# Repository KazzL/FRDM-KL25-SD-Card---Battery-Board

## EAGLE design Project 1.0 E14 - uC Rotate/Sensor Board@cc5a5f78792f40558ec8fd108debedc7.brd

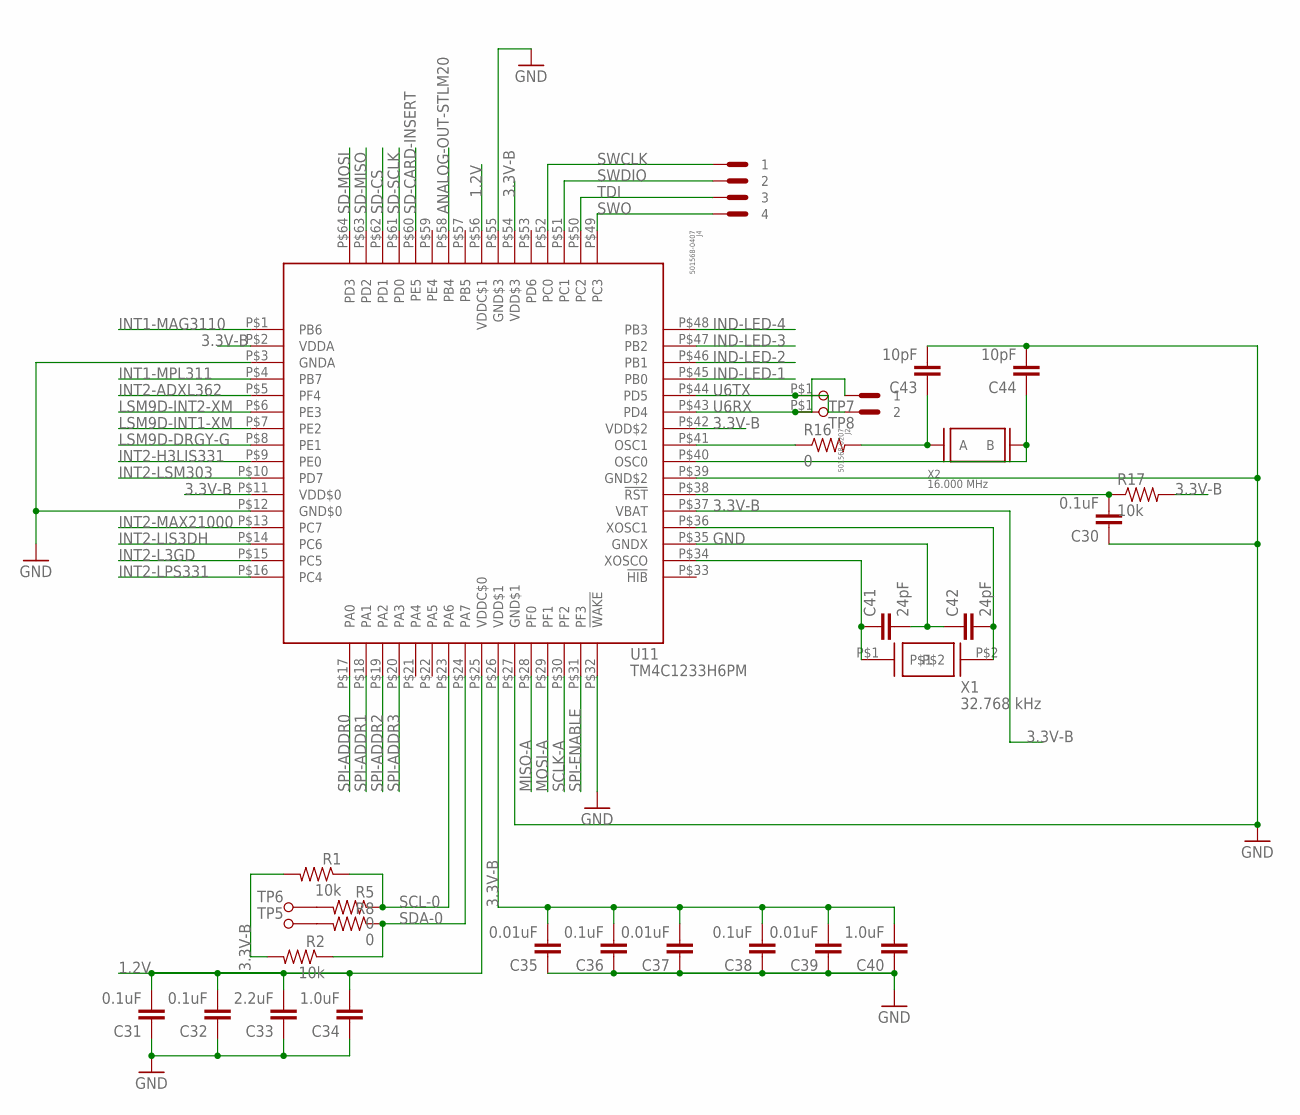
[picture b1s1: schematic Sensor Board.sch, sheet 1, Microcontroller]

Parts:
C30, C31, C32, C36, C38: 0.1uF; C0402
C33: 2.2uF; C0402
C34, C40: 1.0uF; C0402
C35, C37, C39: 0.01uF; C0402
C41, C42: 24pF; C0402
C43, C44: 10pF; C0402
J2: 501568-0207
J4: 501568-0407
R1, R2, R17: 10k; R0402
R5, R8, R16: 0; R0402
TP5, TP6, TP7, TP8: TESTPAD(ROUND)
U11: TM4C1233H6PM; S-PQFP-G64
X1: 32.768 kHz; 2-SMD(3.2X1.5)
X2: 16.000 MHz; 4-SMD(3.2X2.5)

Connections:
1.2V: C31.2, C32.2, C33.2, C34.2, U11.P$25 (VDDC$0), U11.P$56 (VDDC$1)
3.3V-B: C35.2, C36.2, C37.2, C38.2, C39.2, C40.2, R1.2, R2.2, R17.2, U11.P$2 (VDDA), U11.P$11 (VDD$0), U11.P$26 (VDD$1), U11.P$37 (VBAT), U11.P$42 (VDD$2), U11.P$54 (VDD$3); also elsewhere on the board
ANALOG-OUT-STLM20: U11.P$58 (PB4); also elsewhere on the board
GND: C30.1, C31.1, C32.1, C33.1, C34.1, C35.1, C36.1, C37.1, C38.1, C39.1, C40.1, C41.2, C42.1, C43.2, C44.2, U11.P$3 (GNDA), U11.P$12 (GND$0), U11.P$27 (GND$1), U11.P$32 (!WAKE), U11.P$35 (GNDX), U11.P$39 (GND$2), U11.P$55 (GND$3); also elsewhere on the board
IND-LED-1: U11.P$45 (PB0); also elsewhere on the board
IND-LED-2: U11.P$46 (PB1); also elsewhere on the board
IND-LED-3: U11.P$47 (PB2); also elsewhere on the board
IND-LED-4: U11.P$48 (PB3); also elsewhere on the board
INT1-MAG3110: U11.P$1 (PB6); also elsewhere on the board
INT1-MPL311: U11.P$4 (PB7); also elsewhere on the board
INT2-ADXL362: U11.P$5 (PF4); also elsewhere on the board
INT2-H3LIS331: U11.P$9 (PE0); also elsewhere on the board
INT2-L3GD: U11.P$15 (PC5); also elsewhere on the board
INT2-LIS3DH: U11.P$14 (PC6); also elsewhere on the board
INT2-LPS331: U11.P$16 (PC4); also elsewhere on the board
INT2-LSM303: U11.P$10 (PD7); also elsewhere on the board
INT2-MAX21000: U11.P$13 (PC7); also elsewhere on the board
LSM9D-DRGY-G: U11.P$8 (PE1); also elsewhere on the board
LSM9D-INT1-XM: U11.P$7 (PE2); also elsewhere on the board
LSM9D-INT2-XM: U11.P$6 (PE3); also elsewhere on the board
MISO-A: U11.P$28 (PF0); also elsewhere on the board
MOSI-A: U11.P$29 (PF1); also elsewhere on the board
unnamed: C30.2, R17.1, U11.P$38 (!RST)
unnamed: C42.2, U11.P$36 (XOSC1), X1.P$2
unnamed: C41.1, U11.P$34 (XOSCO), X1.P$1
unnamed: C43.1, R16.2, X2.P$1 (A)
unnamed: C44.1, U11.P$40 (OSC0), X2.P$3 (B)
unnamed: R16.1, U11.P$41 (OSC1)
unnamed: R5.2, TP6.P$1
unnamed: R8.2, TP5.P$1
SCL-0: R1.1, R5.1, U11.P$23 (PA6); also elsewhere on the board
SCLK-A: U11.P$30 (PF2); also elsewhere on the board
SD-CARD-INSERT: U11.P$60 (PE5); also elsewhere on the board
SD-CS: U11.P$62 (PD1); also elsewhere on the board
SD-MISO: U11.P$63 (PD2); also elsewhere on the board
SD-MOSI: U11.P$64 (PD3); also elsewhere on the board
SD-SCLK: U11.P$61 (PD0); also elsewhere on the board
SDA-0: R2.1, R8.1, U11.P$24 (PA7); also elsewhere on the board
SPI-ADDR0: U11.P$17 (PA0); also elsewhere on the board
SPI-ADDR1: U11.P$18 (PA1); also elsewhere on the board
SPI-ADDR2: U11.P$19 (PA2); also elsewhere on the board
SPI-ADDR3: U11.P$20 (PA3); also elsewhere on the board
SPI-ENABLE: U11.P$31 (PF3); also elsewhere on the board
SWCLK: J4.P$1 (1), U11.P$52 (PC0)
SWDIO: J4.P$2 (2), U11.P$51 (PC1)
SWO: J4.P$4 (4), U11.P$49 (PC3)
TDI: J4.P$3 (3), U11.P$50 (PC2)
U6RX: J2.P$1 (1), TP8.P$1, U11.P$43 (PD4)
U6TX: J2.P$2 (2), TP7.P$1, U11.P$44 (PD5)

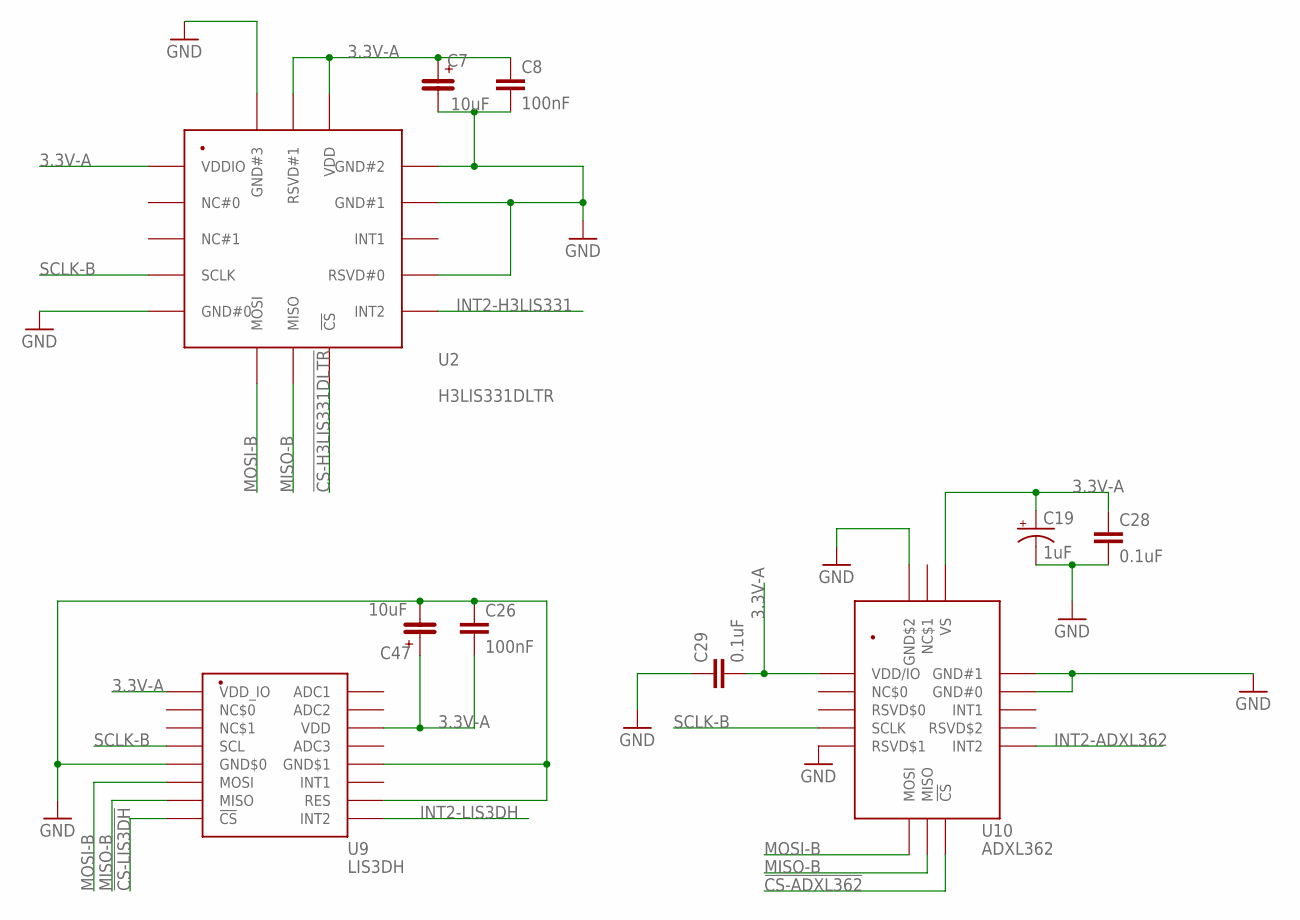
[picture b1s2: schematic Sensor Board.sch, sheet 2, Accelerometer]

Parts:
C7, C47: 10uF; 4.3X7.3SMD
C8, C26: 100nF; C0402
C19: 1uF; EIA6032
C28, C29: 0.1uF; C0402
U2: H3LIS331DLTR; LGA-16(3X3)
U9: LIS3DH; LGA-16(3X3)
U10: ADXL362; LGA-16(3X3.25)

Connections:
3.3V-A: C7.P$1, C8.1, C19.P$1 (+), C26.2, C28.1, C29.2, C47.P$1, U2.P$1 (VDDIO), U2.P$14 (VDD), U2.P$15 (RSVD#1), U9.P$1 (VDD_IO), U9.P$14 (VDD), U10.P$1 (VDD/IO), U10.P$14 (VS); also elsewhere on the board
!CS-ADXL362: U10.P$8 (!CS); also elsewhere on the board
!CS-H3LIS331DLTR: U2.P$8 (!CS); also elsewhere on the board
!CS-LIS3DH: U9.P$8 (!CS); also elsewhere on the board
GND: C7.P$2, C8.2, C19.P$2 (-), C26.1, C28.2, C29.1, C47.P$2, U2.P$5 (GND#0), U2.P$10 (RSVD#0), U2.P$12 (GND#1), U2.P$13 (GND#2), U2.P$16 (GND#3), U9.P$5 (GND$0), U9.P$10 (RES), U9.P$12 (GND$1), U10.P$5 (RSVD$1), U10.P$12 (GND#0), U10.P$13 (GND#1), U10.P$16 (GND$2); also elsewhere on the board
INT2-ADXL362: U10.P$9 (INT2); also elsewhere on the board
INT2-H3LIS331: U2.P$9 (INT2); also elsewhere on the board
INT2-LIS3DH: U9.P$9 (INT2); also elsewhere on the board
MISO-B: U2.P$7 (MISO), U9.P$7 (MISO), U10.P$7 (MISO); also elsewhere on the board
MOSI-B: U2.P$6 (MOSI), U9.P$6 (MOSI), U10.P$6 (MOSI); also elsewhere on the board
SCLK-B: U2.P$4 (SCLK), U9.P$4 (SCL), U10.P$4 (SCLK); also elsewhere on the board

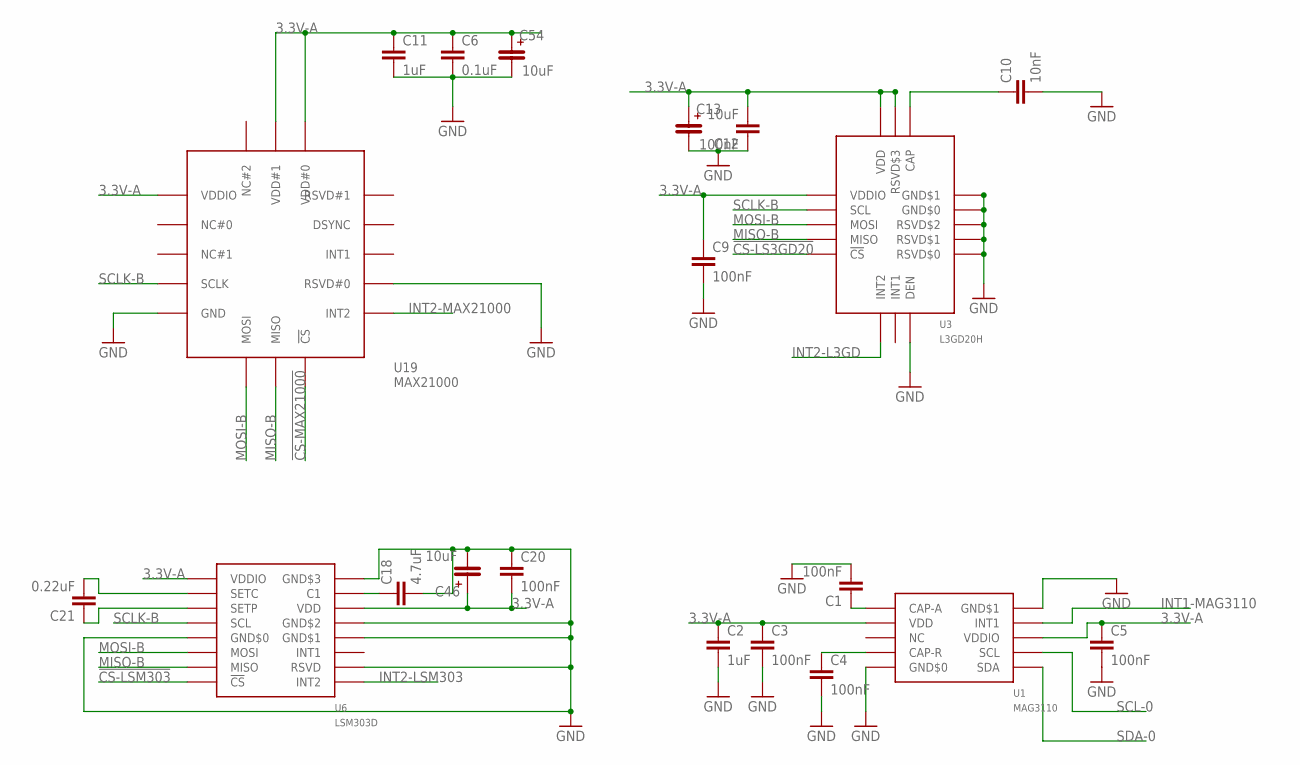
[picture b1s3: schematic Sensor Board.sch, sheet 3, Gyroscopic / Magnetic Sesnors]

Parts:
C1, C3, C4, C5, C9, C20: 100nF; C0402
C2, C11: 1uF; C0402
C6: 0.1uF; C0402
C10: 10nF; C0402
C12: 10uF; C0402
C13: 100nF; 4.3X7.3SMD
C18: 4.7uF; C0402
C21: 0.22uF; C0402
C46, C54: 10uF; 4.3X7.3SMD
U1: MAG3110; DFN-10(2X2)
U3: L3GD20H; LGA-16(3X3)
U6: LSM303D; LGA-16(3X3)
U19: MAX21000; LGA-16(3X3)

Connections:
3.3V-A: C2.1, C3.1, C5.1, C6.1, C9.1, C11.1, C12.2, C13.P$1, C20.2, C46.P$1, C54.P$1, U1.P$2 (VDD), U1.P$8 (VDDIO), U3.P$1 (VDDIO), U3.P$15 (RSVD$3), U3.P$16 (VDD), U6.P$1 (VDDIO), U6.P$14 (VDD), U19.P$1 (VDDIO), U19.P$14 (VDD#0), U19.P$15 (VDD#1); also elsewhere on the board
!CS-LS3GD20: U3.P$5 (!CS); also elsewhere on the board
!CS-LSM303: U6.P$8 (!CS); also elsewhere on the board
!CS-MAX21000: U19.P$8 (!CS); also elsewhere on the board
GND: C1.2, C2.2, C3.2, C4.2, C5.2, C6.2, C9.2, C10.2, C11.2, C12.1, C13.P$2, C18.2, C20.1, C46.P$2, C54.P$2, U1.P$5 (GND$0), U1.P$10 (GND$1), U3.P$8 (DEN), U3.P$9 (RSVD$0), U3.P$10 (RSVD$1), U3.P$11 (RSVD$2), U3.P$12 (GND$0), U3.P$13 (GND$1), U6.P$5 (GND$0), U6.P$10 (RSVD), U6.P$12 (GND$1), U6.P$13 (GND$2), U6.P$16 (GND$3), U19.P$5 (GND), U19.P$10 (RSVD#0); also elsewhere on the board
INT1-MAG3110: U1.P$9 (INT1); also elsewhere on the board
INT2-L3GD: U3.P$6 (INT2); also elsewhere on the board
INT2-LSM303: U6.P$9 (INT2); also elsewhere on the board
INT2-MAX21000: U19.P$9 (INT2); also elsewhere on the board
MISO-B: U3.P$4 (MISO), U6.P$7 (MISO), U19.P$7 (MISO); also elsewhere on the board
MOSI-B: U3.P$3 (MOSI), U6.P$6 (MOSI), U19.P$6 (MOSI); also elsewhere on the board
unnamed: C1.1, U1.P$1 (CAP-A)
unnamed: C4.1, U1.P$4 (CAP-R)
unnamed: C10.1, U3.P$14 (CAP)
unnamed: C18.1, U6.P$15 (C1)
unnamed: C21.2, U6.P$2 (SETC)
unnamed: C21.1, U6.P$3 (SETP)
SCL-0: U1.P$7 (SCL); also elsewhere on the board
SCLK-B: U3.P$2 (SCL), U6.P$4 (SCL), U19.P$4 (SCLK); also elsewhere on the board
SDA-0: U1.P$6 (SDA); also elsewhere on the board

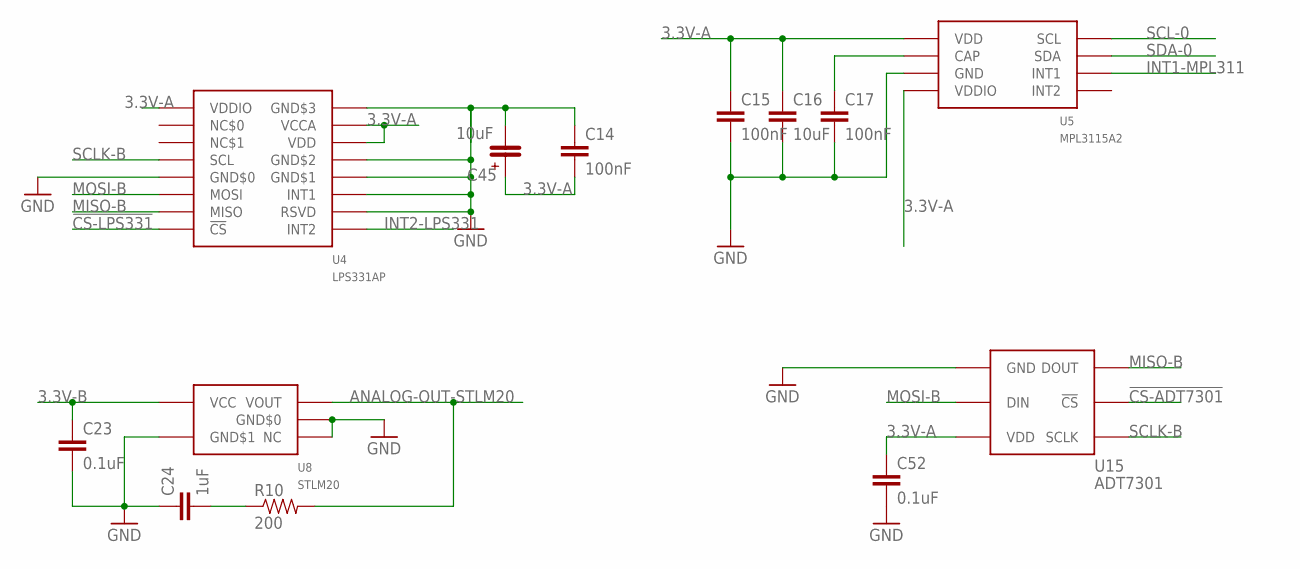
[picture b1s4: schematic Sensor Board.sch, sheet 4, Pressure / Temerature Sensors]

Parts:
C14, C15, C17: 100nF; C0402
C16: 10uF; C0402
C23, C52: 0.1uF; C0402
C24: 1uF; C0402
C45: 10uF; 4.3X7.3SMD
R10: 200; R0402
U4: LPS331AP; LGA-16(3X3)
U5: MPL3115A2; LGA-8(5X3)
U8: STLM20; SOT323-5L
U15: ADT7301; SOT23-6

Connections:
3.3V-A: C14.2, C15.1, C16.1, C45.P$1, C52.1, U4.P$1 (VDDIO), U4.P$14 (VDD), U4.P$15 (VCCA), U5.P$1 (VDD), U5.P$4 (VDDIO), U15.P$3 (VDD); also elsewhere on the board
3.3V-B: C23.1, U8.P$4 (VCC); also elsewhere on the board
!CS-ADT7301: U15.P$5 (!CS); also elsewhere on the board
!CS-LPS331: U4.P$8 (!CS); also elsewhere on the board
ANALOG-OUT-STLM20: R10.2, U8.P$3 (VOUT); also elsewhere on the board
GND: C14.1, C15.2, C16.2, C17.2, C23.2, C24.1, C45.P$2, C52.2, U4.P$5 (GND$0), U4.P$10 (RSVD), U4.P$11 (INT1), U4.P$12 (GND$1), U4.P$13 (GND$2), U4.P$16 (GND$3), U5.P$3 (GND), U8.P$1 (NC), U8.P$2 (GND$0), U8.P$5 (GND$1), U15.P$1 (GND); also elsewhere on the board
INT1-MPL311: U5.P$6 (INT1); also elsewhere on the board
INT2-LPS331: U4.P$9 (INT2); also elsewhere on the board
MISO-B: U4.P$7 (MISO), U15.P$6 (DOUT); also elsewhere on the board
MOSI-B: U4.P$6 (MOSI), U15.P$2 (DIN); also elsewhere on the board
unnamed: C17.1, U5.P$2 (CAP)
unnamed: C24.2, R10.1
SCL-0: U5.P$8 (SCL); also elsewhere on the board
SCLK-B: U4.P$4 (SCL), U15.P$4 (SCLK); also elsewhere on the board
SDA-0: U5.P$7 (SDA); also elsewhere on the board

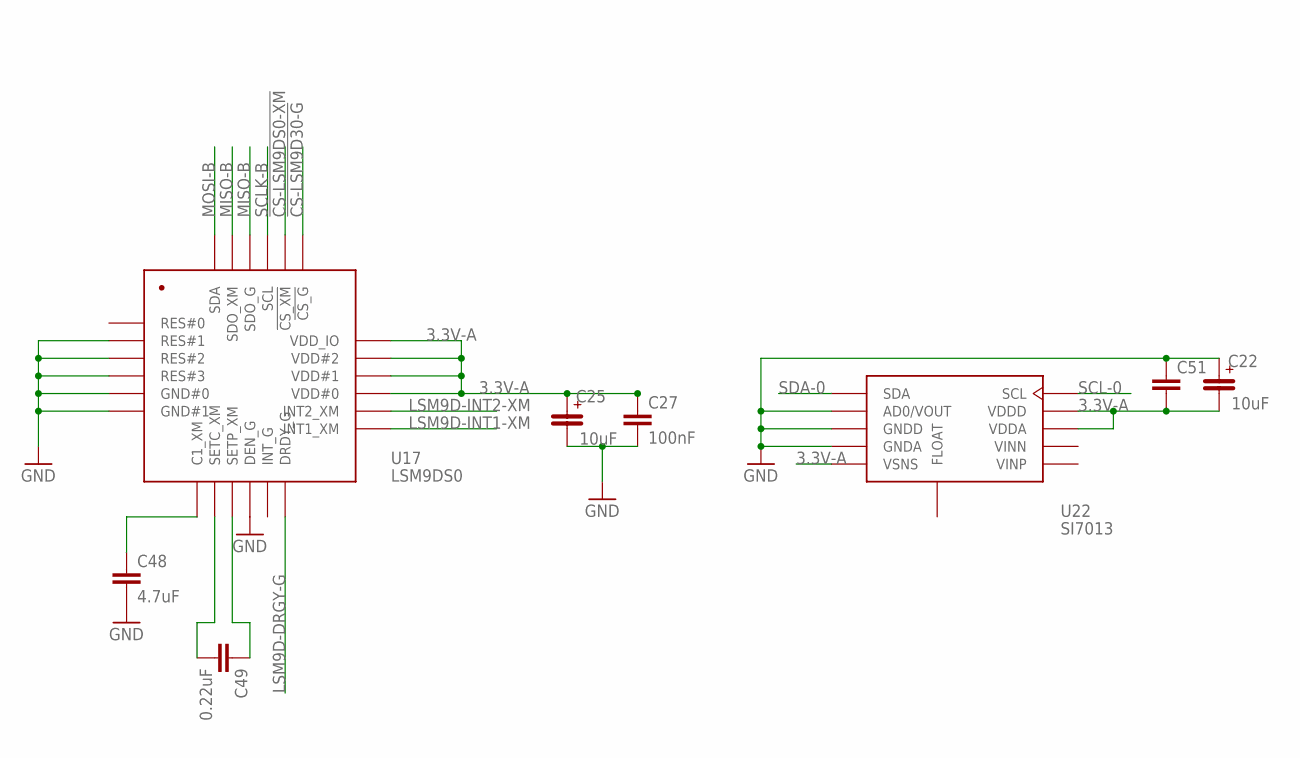
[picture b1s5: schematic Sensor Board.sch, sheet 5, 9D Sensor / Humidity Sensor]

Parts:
C22, C25: 10uF; 4.3X7.3SMD
C27: 100nF; C0402
C48: 4.7uF; C0402
C49: 0.22uF; C0402
C51: CAPACITOR0402; C0402
U17: LSM9DS0; LGA-24(4X4)
U22: SI7013; DFN-10(3X3)

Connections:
3.3V-A: C22.P$2, C25.P$1, C27.1, C51.2, U17.P$15 (VDD#0), U17.P$16 (VDD#1), U17.P$17 (VDD#2), U17.P$18 (VDD_IO), U22.P$5 (VSNS), U22.P$8 (VDDA), U22.P$9 (VDDD); also elsewhere on the board
!CS-LSM9D30-G: U17.P$19 (!CS_G); also elsewhere on the board
!CS-LSM9DS0-XM: U17.P$20 (!CS_XM); also elsewhere on the board
GND: C22.P$1, C25.P$2, C27.2, C48.2, C51.1, U17.P$2 (RES#1), U17.P$3 (RES#2), U17.P$4 (RES#3), U17.P$5 (GND#0), U17.P$6 (GND#1), U17.P$10 (DEN_G), U22.P$2 (AD0/VOUT), U22.P$3 (GNDD), U22.P$4 (GNDA); also elsewhere on the board
LSM9D-DRGY-G: U17.P$12 (DRDY_G); also elsewhere on the board
LSM9D-INT1-XM: U17.P$13 (INT1_XM); also elsewhere on the board
LSM9D-INT2-XM: U17.P$14 (INT2_XM); also elsewhere on the board
MISO-B: U17.P$22 (SDO_G), U17.P$23 (SDO_XM); also elsewhere on the board
MOSI-B: U17.P$24 (SDA); also elsewhere on the board
unnamed: C48.1, U17.P$7 (C1_XM)
unnamed: C49.2, U17.P$8 (SETC_XM)
unnamed: C49.1, U17.P$9 (SETP_XM)
SCL-0: U22.P$10 (SCL); also elsewhere on the board
SCLK-B: U17.P$21 (SCL); also elsewhere on the board
SDA-0: U22.P$1 (SDA); also elsewhere on the board

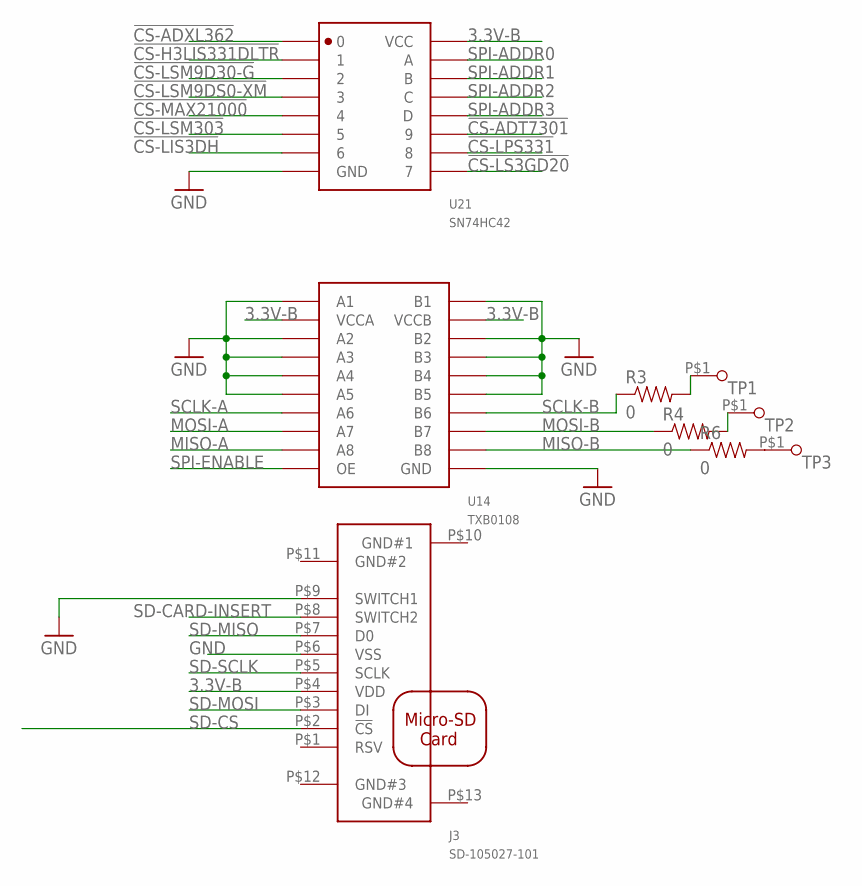
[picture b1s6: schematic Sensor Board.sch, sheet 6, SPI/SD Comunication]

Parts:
J3: SD-105027-101; SD-105027-1001
R3, R4, R6: 0; R0402
TP1, TP2, TP3: TESTPAD(ROUND)
U14: TXB0108; TSSOP-(PW)-20
U21: SN74HC42; SOIC-16

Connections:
3.3V-B: J3.P$4 (VDD), U14.P$2 (VCCA), U14.P$19 (VCCB), U21.P$16 (VCC); also elsewhere on the board
!CS-ADT7301: U21.P$11 (9); also elsewhere on the board
!CS-ADXL362: U21.P$1 (0); also elsewhere on the board
!CS-H3LIS331DLTR: U21.P$2 (1); also elsewhere on the board
!CS-LIS3DH: U21.P$7 (6); also elsewhere on the board
!CS-LPS331: U21.P$10 (8); also elsewhere on the board
!CS-LS3GD20: U21.P$9 (7); also elsewhere on the board
!CS-LSM9D30-G: U21.P$3 (2); also elsewhere on the board
!CS-LSM9DS0-XM: U21.P$4 (3); also elsewhere on the board
!CS-LSM303: U21.P$6 (5); also elsewhere on the board
!CS-MAX21000: U21.P$5 (4); also elsewhere on the board
GND: J3.P$6 (VSS), J3.P$9 (SWITCH1), U14.P$1 (A1), U14.P$3 (A2), U14.P$4 (A3), U14.P$5 (A4), U14.P$6 (A5), U14.P$11 (GND), U14.P$15 (B5), U14.P$16 (B4), U14.P$17 (B3), U14.P$18 (B2), U14.P$20 (B1), U21.P$8 (GND); also elsewhere on the board
MISO-A: U14.P$9 (A8); also elsewhere on the board
MISO-B: R6.1, U14.P$12 (B8); also elsewhere on the board
MOSI-A: U14.P$8 (A7); also elsewhere on the board
MOSI-B: R4.1, U14.P$13 (B7); also elsewhere on the board
unnamed: R3.2, TP1.P$1
unnamed: R4.2, TP2.P$1
unnamed: R6.2, TP3.P$1
SCLK-A: U14.P$7 (A6); also elsewhere on the board
SCLK-B: R3.1, U14.P$14 (B6); also elsewhere on the board
SD-CARD-INSERT: J3.P$8 (SWITCH2); also elsewhere on the board
SD-CS: J3.P$2 (!CS); also elsewhere on the board
SD-MISO: J3.P$7 (D0); also elsewhere on the board
SD-MOSI: J3.P$3 (DI); also elsewhere on the board
SD-SCLK: J3.P$5 (SCLK); also elsewhere on the board
SPI-ADDR0: U21.P$15 (A); also elsewhere on the board
SPI-ADDR1: U21.P$14 (B); also elsewhere on the board
SPI-ADDR2: U21.P$13 (C); also elsewhere on the board
SPI-ADDR3: U21.P$12 (D); also elsewhere on the board
SPI-ENABLE: U14.P$10 (OE); also elsewhere on the board

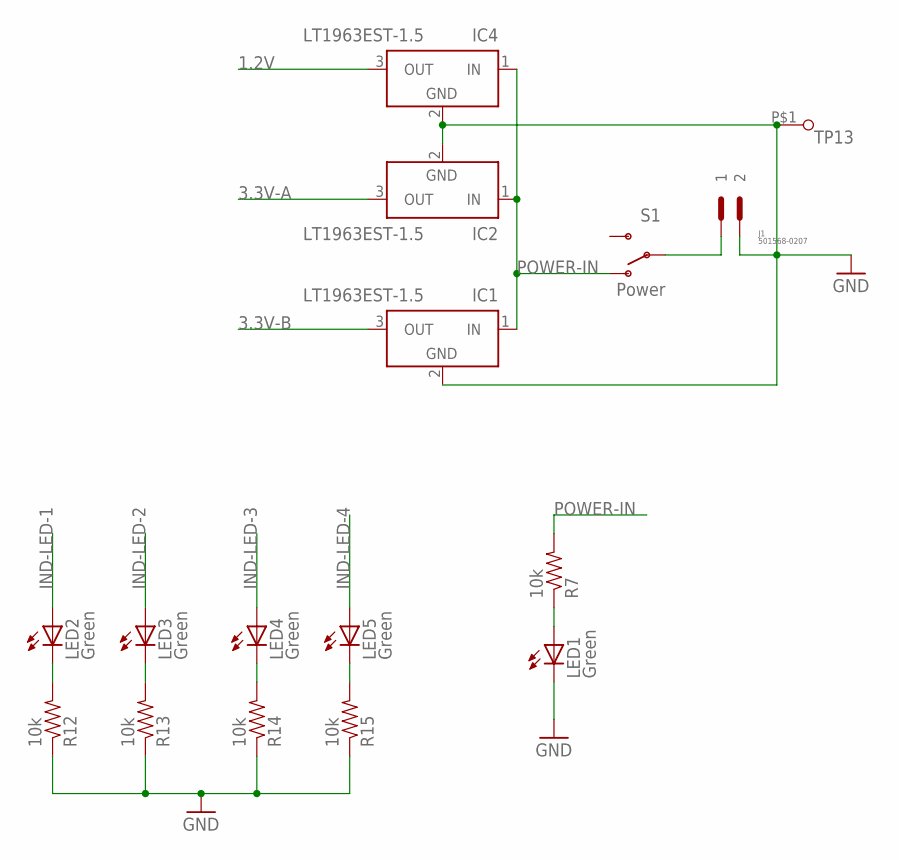
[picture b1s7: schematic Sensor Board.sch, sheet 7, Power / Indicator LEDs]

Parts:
IC1, IC2, IC4: LT1963EST-1.5; SOT223
J1: 501568-0207
LED1, LED2, LED3, LED4, LED5: Green; LED_SML0603
R7, R12, R13, R14, R15: 10k; R0402
S1: Power; SWITCH-SPST-SMD-A
TP13: TESTPAD(ROUND)

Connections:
GND: IC1.2 (GND), IC2.2 (GND), IC4.2 (GND), J1.P$2 (2), LED1.C, R12.1, R13.1, R14.1, R15.1, TP13.P$1; also elsewhere on the board
IND-LED-1: LED2.A; also elsewhere on the board
IND-LED-2: LED3.A; also elsewhere on the board
IND-LED-3: LED4.A; also elsewhere on the board
IND-LED-4: LED5.A; also elsewhere on the board
unnamed: J1.P$1 (1), S1.2
unnamed: LED5.C, R15.2
unnamed: LED1.A, R7.1
unnamed: LED4.C, R14.2
unnamed: LED3.C, R13.2
unnamed: LED2.C, R12.2
POWER-IN: IC1.1 (IN), IC2.1 (IN), IC4.1 (IN), R7.2, S1.1 (O); also elsewhere on the board

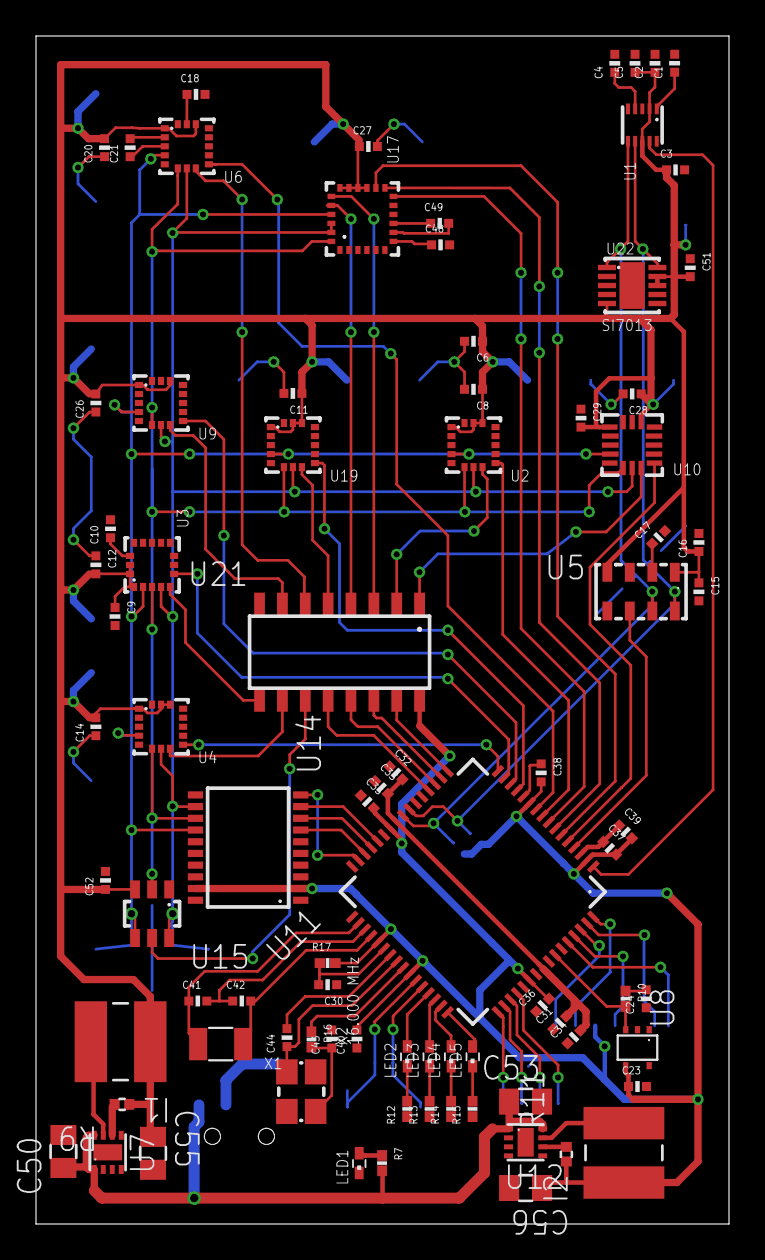
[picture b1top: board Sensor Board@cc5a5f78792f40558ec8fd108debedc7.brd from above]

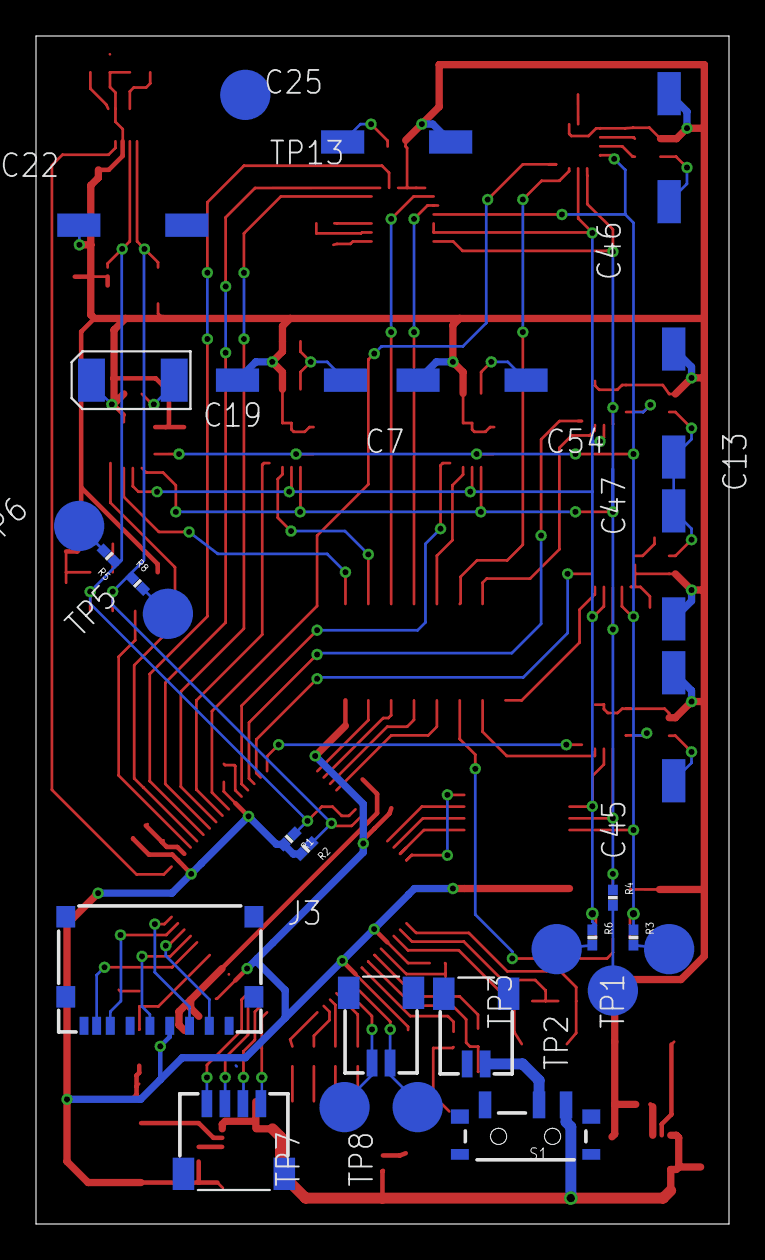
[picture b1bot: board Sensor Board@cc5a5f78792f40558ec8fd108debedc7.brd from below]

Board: 4 copper layers, 38.5 x 66.0 mm, 113 parts (29 on the bottom side), 88 nets.

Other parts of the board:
C50, C53: GRM21BR60J106ME19L; 0805
C55, C56: C2012X5R0J226M; 0805
I1, I2: SDR0403-1R0ML; SDR0403
R9, R11: CRCW0402178KFKED; 0402
U7, U12: TPS62082DSGR; S-PWSON-N8

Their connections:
3.3V-A: C55.1, I1.1, R9.1; also elsewhere on the board
3.3V-B: C56.1, I2.1, R11.1; also elsewhere on the board
GND: C50.2, C53.2, C55.2, C56.2, U7.2, U7.3, U7.9, U12.2, U12.3, U12.9; also elsewhere on the board
unnamed: I1.2, U7.7
unnamed: R9.2, U7.6
unnamed: I2.2, U12.7
unnamed: R11.2, U12.6
POWER-IN: C50.1, C53.1, U7.1, U7.8, U12.1, U12.8; also elsewhere on the board

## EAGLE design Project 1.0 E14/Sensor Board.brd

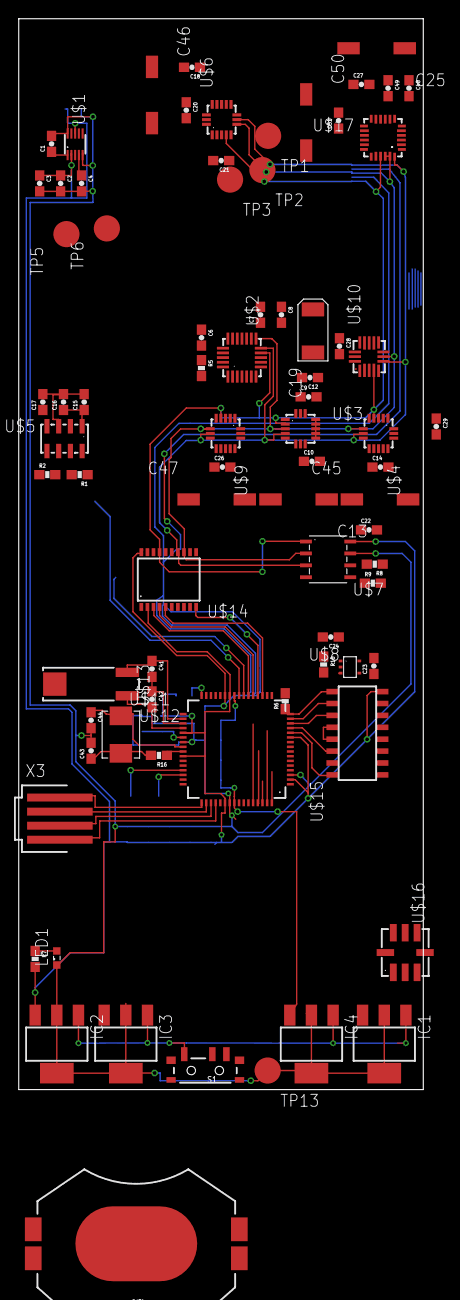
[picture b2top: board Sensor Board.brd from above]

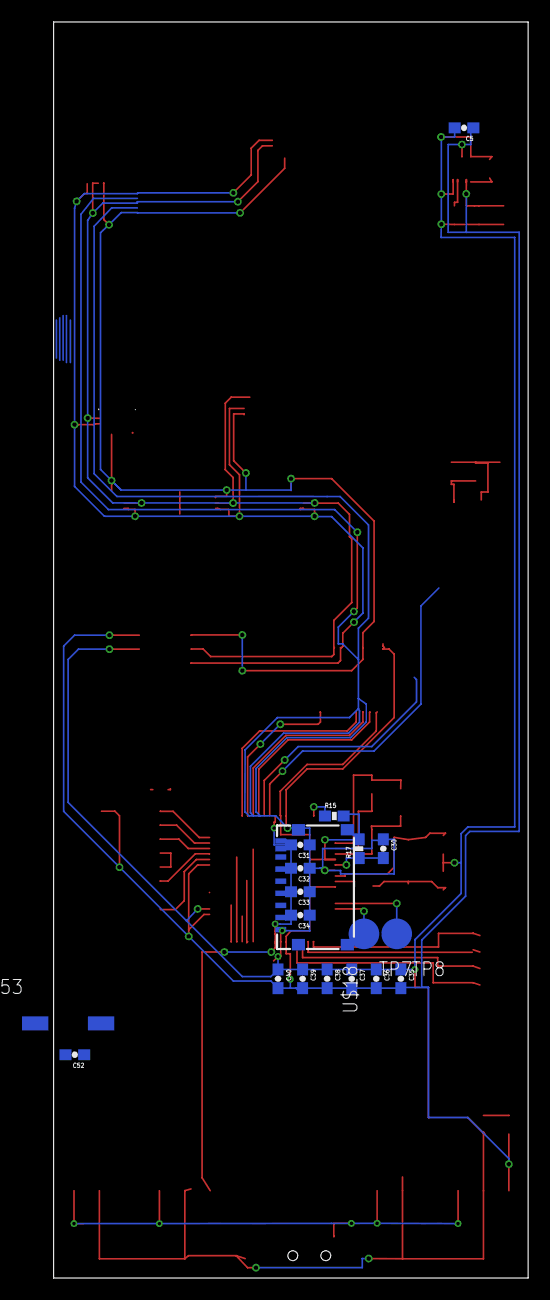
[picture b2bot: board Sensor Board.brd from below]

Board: 4 copper layers, 43.2 x 114.3 mm, 97 parts (19 on the bottom side), 66 nets.

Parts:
BAT1: 20mm coincell; BATTCON_20MM_4LEGS
C1, C3, C4, C5, C7, C9, C14, C15, C17, C20, C26, C27, C51: 100nF; 0603-CAP
C2, C6, C8, C24: 1uF; 0603-CAP
C10: 10nF; 0603-CAP
C12, C16: 10uF; 0603-CAP
C13: 100nF; 4.3X7.3SMD
C18, C48: 4.7uF; 0603-CAP
C19: 1uF; EIA6032
C21, C49: 0.22uF; 0603-CAP
C22, C23, C28, C29, C30, C31, C32, C34, C35, C37, C39, C52: 0.1uF; 0603-CAP
C25, C45, C46, C47, C50: 10uF; 4.3X7.3SMD
C33: 2.2uF; 0603-CAP
C36, C38, C40: 0.01uF; 0603-CAP
C41, C42: 24pF; 0603-CAP
C43, C44: 10pF; 0603-CAP
C53: 4.7uF; 4.3X7.3SMD
IC1, IC2, IC3, IC4: LT1963EST-1.5; SOT223
LED1: Green; LED_SML0603
R1, R2, R7, R8, R9, R17: 10k; 0603-RES
R5: 4.7k; 0603-RES
R6, R16: 0; 0603-RES
R10: 200; 0603-RES
R15: 1M; 0603-RES
S1: Power; SWITCH-SPST-SMD-A
TP1, TP2, TP3, TP5, TP6, TP7, TP8, TP13: TESTPAD(ROUND)
U$1: MAG3110_HS; DFN-10(2X2)_HS
U$2: FXAS21000_HS; QFN-24(4X4)_HS
U$3: L3GD20H_HS; LGA-16(3X3)_HS
U$4: LPS331AP_HS; LGA-16(3X3)_HS
U$5: MPL3115A2_HS; LGA-8(5X3)_HS
U$6: LSM303D_HS; LGA-16(3X3)_HS
U$7: ADT7310; SOIC-8(5X6.2)
U$8: STLM20; SOT323-5L
U$9: LIS3DH; LGA-16(3X3)_HS
U$10: ADXL362; LGA-16(3X3.25)_HS
U$11: TM4C1233H6PM; S-PQFP-G64
U$12: 32.768 kHz; CYLINDRICAL-(1.9DIAX6L)
U$13: 16.000 MHz; 2-SMD
U$14: TXB0108; TSSOP-(PW)-20
U$15: CD74HC138; SOIC-16
U$16: ADXL78; LCC-8(5X5)_HS
U$17: LSM9DS0_HS; LGA-24(4X4)_HS
U$18: SD-105027-101
X3: 87438-04

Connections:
1.2V: C31.2, C32.2, C33.2, C34.2, IC4.3, U$11.P$25, U$11.P$56
3.0V: C50.P$1, C51.1, IC1.3, U$17.P$18
3.3V: C2.1, C3.1, C5.1, C6.2, C8.2, C9.1, C12.2, C13.P$1, C14.2, C19.P$1, C20.2, C22.1, C23.1, C25.P$1, C26.2, C27.1, C28.1, C29.2, C35.2, C36.2, C37.2, C38.2, C39.2, C40.2, C45.P$1, C46.P$1, C47.P$1, IC2.3, R1.2, R2.2, R5.2, R6.2, R7.2, R8.2, R9.2, R15.2, R17.2, U$1.P$2, U$1.P$8, U$2.P$15, U$2.P$18, U$3.P$1, U$3.P$15, U$3.P$16, U$4.P$1, U$4.P$14, U$4.P$15, U$5.P$4, U$6.P$1, U$6.P$14, U$7.P$8, U$8.P$4, U$9.P$1, U$9.P$14, U$10.P$1, U$10.P$14, U$11.P$2, U$11.P$11, U$11.P$26, U$11.P$37, U$11.P$42, U$11.P$54, U$14.P$2, U$14.P$12, U$15.P$16, U$17.P$15, U$17.P$16, U$17.P$17, U$18.P$4
5.0V: C52.1, C53.P$1, IC3.3, U$16.P$7, U$16.P$8
ANALOG-OUT-ADXL78: U$11.P$6, U$16.P$6
ANALOG-OUT-STLM20: R10.2, U$8.P$3, U$11.P$1
CS-ADT7310: U$7.P$4, U$15.P$9
CS-ADXL362: U$10.P$8, U$15.P$12
CS-ENABLE: U$11.P$13, U$15.P$6
CS-FXAS: U$2.P$17, U$15.P$13
CS-LIS3DH: U$9.P$8, U$15.P$14
CS-LPS331: U$4.P$8, U$15.P$11
CS-LSGD: U$3.P$5, U$15.P$15
CS-LSM9D30-G: U$15.P$7, U$17.P$19
CS-LSM303: U$6.P$8, U$15.P$10
CT-ADT7310: R8.1, U$7.P$6
GND: BAT1.2, C1.2, C2.2, C3.2, C4.2, C5.2, C6.1, C7.2, C8.1, C9.2, C10.2, C12.1, C13.P$2, C14.1, C15.2, C16.2, C17.2, C18.2, C19.P$2, C20.1, C22.2, C23.2, C24.1, C25.P$2, C26.1, C27.2, C28.2, C29.1, C30.1, C31.1, C32.1, C33.1, C34.1, C35.1, C36.1, C37.1, C38.1, C39.1, C40.1, C43.2, C44.2, C45.P$2, C46.P$2, C47.P$2, C48.2, C50.P$2, C51.2, C52.2, C53.P$2, IC1.2, IC1.4, IC2.2, IC2.4, IC3.2, IC3.4, IC4.2, IC4.4, LED1.C, TP13.P$1, U$1.P$5, U$1.P$10, U$2.P$1, U$2.P$5, U$2.P$6, U$2.P$7, U$2.P$8, U$2.P$9, U$2.P$10, U$2.P$14, U$2.P$19, U$2.P$20, U$2.P$21, U$2.P$22, U$2.P$23, U$2.P$24, U$3.P$9, U$3.P$10, U$3.P$11, U$3.P$12, U$3.P$13, U$4.P$5, U$4.P$10, U$4.P$11, U$4.P$12, U$4.P$13, U$4.P$16, U$5.P$3, U$6.P$5, U$6.P$10, U$6.P$12, U$6.P$13, U$6.P$16, U$7.P$7, U$8.P$2, U$8.P$5, U$9.P$5, U$9.P$10, U$9.P$12, U$10.P$12, U$10.P$13, U$10.P$16, U$11.P$3, U$11.P$12, U$11.P$27, U$11.P$39, U$11.P$55, U$14.P$20, U$15.P$4, U$15.P$5, U$15.P$8, U$16.P$3, U$17.P$2, U$17.P$3, U$17.P$4, U$17.P$5, U$17.P$6, U$18.P$6, U$18.P$9
INT-ADT7310: R9.1, U$7.P$5
MISO-A: U$11.P$21, U$14.P$4
MISO-B: TP2.P$1, U$2.P$13, U$3.P$3, U$4.P$6, U$6.P$6, U$7.P$2, U$9.P$6, U$10.P$7, U$14.P$14, U$17.P$22, U$17.P$23
MOSI-A: U$11.P$22, U$14.P$3
MOSI-B: TP1.P$1, U$2.P$12, U$3.P$4, U$4.P$7, U$6.P$7, U$7.P$3, U$9.P$7, U$10.P$6, U$14.P$13, U$17.P$24
unnamed: C1.1, U$1.P$1
unnamed: C7.1, U$2.P$16
unnamed: C4.1, U$1.P$4
unnamed: C10.1, U$3.P$14
unnamed: C17.1, U$5.P$2
unnamed: C18.1, U$6.P$15
unnamed: C21.2, U$6.P$2
unnamed: C48.1, U$17.P$7
unnamed: C24.2, R10.1
unnamed: C30.2, R17.1, U$11.P$38
unnamed: C42.2, U$11.P$36, U$12.P$2
unnamed: C41.1, U$11.P$34, U$12.P$1
unnamed: C41.2, C42.1, U$11.P$35
unnamed: C43.1, R16.2, U$13.P$1
unnamed: C21.1, U$6.P$3
unnamed: C44.1, U$11.P$40, U$13.P$2
unnamed: R16.1, U$11.P$41
unnamed: R15.1, U$11.P$32
unnamed: BAT1.1, S1.2
unnamed: C49.2, U$17.P$8
unnamed: C49.1, U$17.P$9
unnamed: IC1.1, IC2.1, IC3.1, IC4.1, S1.3
unnamed: C15.1, C16.1, U$5.P$1
unnamed: LED1.A, R7.1
RST_B: R5.1, U$2.P$4
SCL-0: R1.1, TP6.P$1, U$1.P$7, U$5.P$8, U$11.P$23
SCLK-A: U$11.P$19, U$14.P$5
SCLK-B: TP3.P$1, U$2.P$11, U$3.P$2, U$4.P$4, U$6.P$4, U$7.P$1, U$9.P$4, U$10.P$4, U$14.P$15, U$17.P$21
SD-CARD-INSERT: U$11.P$60, U$18.P$8
SD-CS: R6.1, U$11.P$62, U$18.P$2
SD-MISO: U$11.P$63, U$18.P$7
SD-MOSI: U$11.P$64, U$18.P$3
SD-SCLK: U$11.P$61, U$18.P$5
SDA-0: R2.1, TP5.P$1, U$1.P$6, U$5.P$7, U$11.P$24
SPI-ADDR0: U$11.P$16, U$15.P$1
SPI-ADDR1: U$11.P$15, U$15.P$2
SPI-ADDR2: U$11.P$14, U$15.P$3
SPI-ENABLE: U$11.P$20, U$14.P$10
SWCLK: U$11.P$52, X3.4
SWDIO: U$11.P$51, X3.3
SWO: U$11.P$49, X3.1
TDI: U$11.P$50, X3.2
U1RX: TP8.P$1, U$11.P$45
U1TX: TP7.P$1, U$11.P$46

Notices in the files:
parts and their libraries:
SparkFun-Passives: Licensing: CC v3.0 Share-Alike You are welcome to use this library for commercial purposes.
